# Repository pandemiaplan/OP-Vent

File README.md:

# OP-Vent
A Simple, Open-Source Ventilator using a Proportional Solenoid Valve

Information gathered from https://op-vent.stanford.edu/ check it out!
Article about information at https://www.engadget.com/nvidia-open-source-ventilator-design-165732445.html

- [Code](/code)
- [PCB Design](/OPVentPCB_V2.2)
- [Documentation](https://op-vent.stanford.edu/docs/need.html)
- [Open-Source Pneumatics](https://op-vent.stanford.edu/open-source_pneumatics.html) / [CAD Model](/models/op-vent_open-source-components.STEP)
- [Off-the-Shelf Pneumatics](https://op-vent.stanford.edu/off-the-shelf_pneumatics.html) / [CAD Model](/models/op-vent_off-the-shelf-components.STEP)

## Video Introduction

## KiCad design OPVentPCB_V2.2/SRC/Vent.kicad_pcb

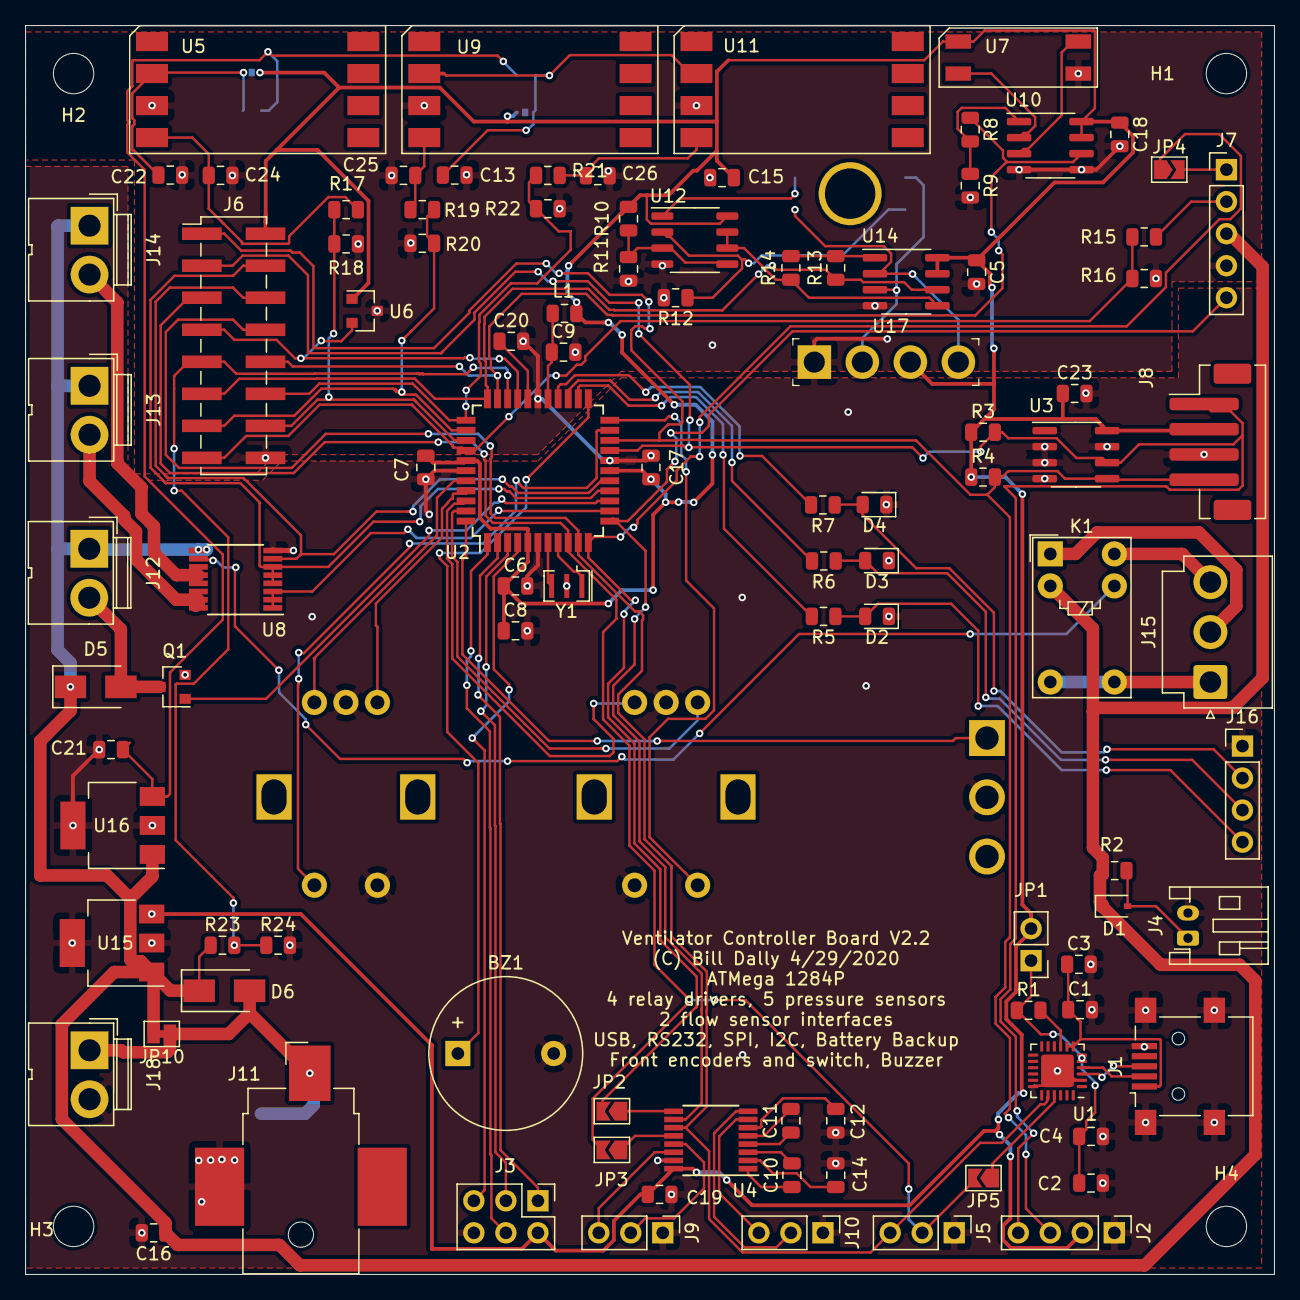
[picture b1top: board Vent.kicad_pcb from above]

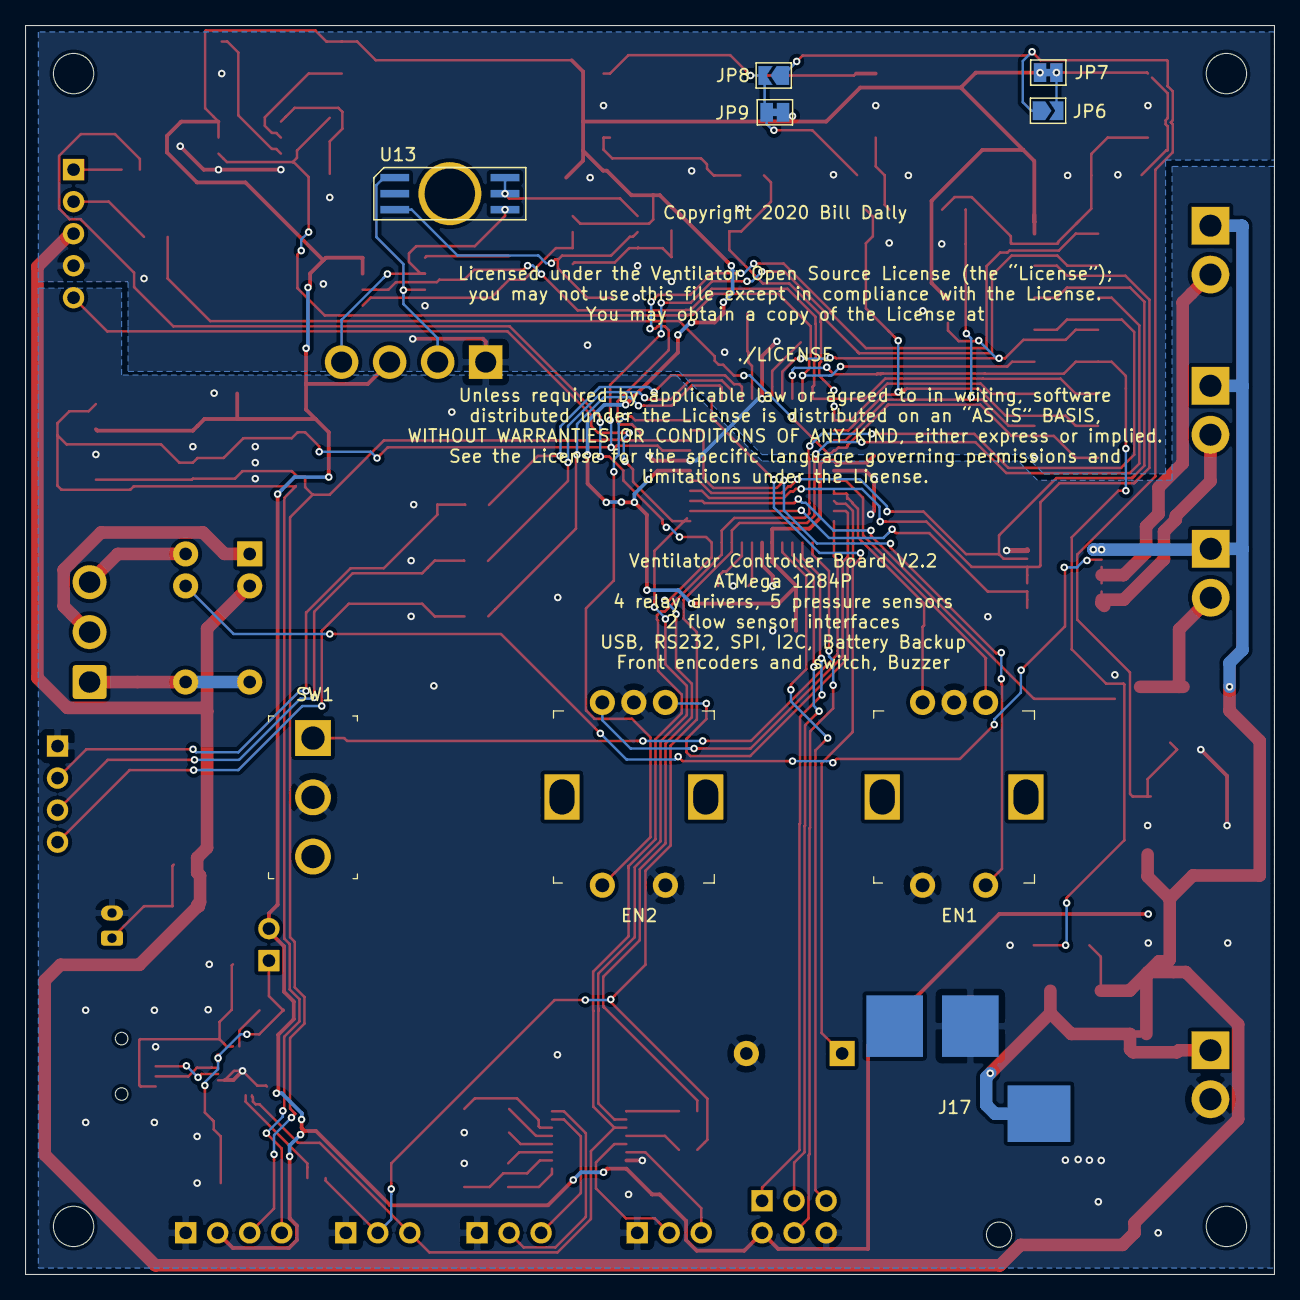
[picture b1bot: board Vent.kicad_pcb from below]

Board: 2 copper layers, 99.1 x 99.1 mm, 113 parts (9 on the bottom side), 88 nets.

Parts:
BZ1: CMI-1295IC-0385T; Buzzer_12x9.5RM7.6
C1, C2: 4.7uF; C_0805_2012Metric
C3, C4, C5, C6, C10, C11, C12, C13, C14, C15, C17, C18, C19, C20, C21, C22, C23: 100nF; C_0805_2012Metric
C7, C16: 10uF; C_0805_2012Metric
C8, C9: 1uF; C_0805_2012Metric
C24, C25, C26: 470pF; C_0805_2012Metric
D1: D_Schottky; D_SOD-323
D2, D3, D4: LED; D_0805_2012Metric
D5, D6: ES1D; D_SMA
EN1: Func_Sel; Rotary_Encoder_Switched_EN11
EN2: Parm_Sel; Rotary_Encoder_Switched_EN11
H1, H2, H3, H4: MountingHole; MountingHole_3.2mm_M3
J1: USB_B_Mini; USB_Mini-B_Lumberg_2486_01_Horizontal
J2: I2C; PinHeader_1x04_P2.54mm_Vertical
J3: Program; PinHeader_2x03_P2.54mm_Vertical
J4: Batt; JST_PH_S2B-PH-K_1x02_P2.00mm_Horizontal
J5: Serial 3.3V; PinHeader_1x03_P2.54mm_Vertical
J6: Test & Spare; PinHeader_2x08_P2.54mm_Vertical_SMD
J7: Siargo; PinHeader_1x05_P2.54mm_Vertical
J8: Honeywell; JST_PH_B4B-PH-SM4-TB_1x04-1MP_P2.00mm_Vertical
J9: RS232; PinHeader_1x03_P2.54mm_Vertical
J10: RS232B; PinHeader_1x03_P2.54mm_Vertical
J11: P12V_Horiz_Front; BarrelJack_CUI_PJ-036AH-SMT_Horizontal
J12: Sol1; JWT_A3963_1x02_P3.96mm_Vertical
J13: Sol2; JWT_A3963_1x02_P3.96mm_Vertical
J14: Sol3; JWT_A3963_1x02_P3.96mm_Vertical
J15: Relay; JST_VH_B3P-VH_1x03_P3.96mm_Vertical
J16: LEDs; PinHeader_1x04_P2.54mm_Vertical
J17: P12V_Vert_Back; BarrelJack_CUI_PJ006A
J18: P12V; JWT_A3963_1x02_P3.96mm_Vertical
JP1: USB Power Jumper; PinHeader_1x02_P2.54mm_Vertical
JP2: RS232B; SolderJumper-2_P1.3mm_Open_TrianglePad1.0x1.5mm
JP3: RS232; SolderJumper-2_P1.3mm_Open_TrianglePad1.0x1.5mm
JP4: Siargo Serial; SolderJumper-2_P1.3mm_Open_TrianglePad1.0x1.5mm
JP5: USB; SolderJumper-2_P1.3mm_Open_TrianglePad1.0x1.5mm
JP6: LP1_5V; SolderJumper-2_P1.3mm_Open_TrianglePad1.0x1.5mm
JP7: LP1_3P3V; SolderJumper-2_P1.3mm_Bridged_Pad1.0x1.5mm
JP8: LP2_5V; SolderJumper-2_P1.3mm_Open_TrianglePad1.0x1.5mm
JP9: LP2_3P3V; SolderJumper-2_P1.3mm_Bridged_Pad1.0x1.5mm
JP10: Power; SolderJumper-2_P1.3mm_Bridged_Pad1.0x1.5mm
K1: G5V-1; Relay_SPDT_Omron_G5V-1
L1: 10uH; L_0805_2012Metric
Q1: PMV20XNE; SOT-23
R1, R3, R4: 2.2K; R_0805_2012Metric
R2, R5, R6, R7: 330; R_0805_2012Metric
R8, R13: 220k; R_0805_2012Metric
R9, R12, R14, R18, R20, R22: 10k; R_0805_2012Metric
R10: 330k; R_0805_2012Metric
R11: 100k; R_0805_2012Metric
R15: 35.7k 0.1%; R_0805_2012Metric
R16: 10k 0.1%; R_0805_2012Metric
R17, R19, R21: 5.1k; R_0805_2012Metric
R23: 26.4K 1%; R_0805_2012Metric
R24: 10k 1%; R_0805_2012Metric
SW1: SW_SPDT; Toggle_Switch_100SP1T1B4M2QE
U1: CP2102N-A01-GQFN24; QFN-24-1EP_4x4mm_P0.5mm_EP2.6x2.6mm
U2: ATmega1284P-AU; TQFP-44_10x10mm_P0.8mm
U3: MC24CM02; SOIC-8_3.9x4.9mm_P1.27mm
U4: MAX3232; TSSOP-16_4.4x5mm_P0.65mm
U5, U11: MP3V5010GP; NXP_Pressure_Sensor
U6: MCP9700AT-ETT; SOT-23
U7: NBPMANN150PGUNV; Honeywell_NBP
U8: ULN2003; TSSOP-16_4.4x5mm_P0.65mm
U9: MPXV5010GP; NXP_Pressure_Sensor
U10, U14: MCP6N11; SOIC-8_3.9x4.9mm_P1.27mm
U12: LMV358; SO-8_3.9x4.9mm_P1.27mm
U13: 2SMPP-03; 2SMPP
U15: 78M33; SOT-223-3_TabPin2
U16: 78L05; SOT-223-3_TabPin2
U17: MX10GP; SIP-4_W3.81mm
Y1: Resonator; Resonator_SMD_muRata_CSTxExxV-3Pin_3.0x1.1mm

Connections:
/A6: J6.9, R23.2, R24.1, U2.31
/A7: J6.7, U2.30, U6.2
/ALARM: BZ1.1, U2.23
/AREF: C20.1, U2.29
/AVCC: C9.1, L1.2, U2.27
/ENC11: EN1.A, U2.40
/ENC12: EN1.B, U2.41
/ENC21: EN2.A, U2.42
/ENC22: EN2.B, U2.43
/FLOW: J6.15, R15.2, R16.1, U2.37
/HP: J6.10, R8.1, U2.32, U10.6
/L1: D2.2, J16.4, R5.1
/L2: D3.2, J16.3, R6.1
/L3: D4.2, J16.2, R7.1
/LED1: R5.2, U2.24
/LED2: R6.2, U2.25
/LED3: R7.2, U2.26
/LP1: J6.14, R17.2, R18.1, U2.36
/LP2: J6.13, R19.2, R20.1, U2.35
/LP3: J6.12, R21.2, R22.1, U2.34
/LP4: J6.11, R13.1, U2.33, U14.6
/MISO: J3.1, U2.2
/MOSI: J3.4, U2.1
/OC1A: Q1.1, U2.14
/OC1B: U2.13, U8.1, U8.2, U8.3
/PD6: J6.4, U2.15, U8.4, U8.5, U8.6
/PD7: J6.6, U2.16, U8.7
/Pressure_Sensors/DLB: R12.1, U12.2, U13.3
/Pressure_Sensors/DLP+: U13.1, U14.3, U17.2
/Pressure_Sensors/DLP-: U13.4, U14.2, U17.4
/Pressure_Sensors/DLPM: R13.2, R14.1, U14.1
/Pressure_Sensors/DLPREF: R14.2, U12.6, U12.7, U14.5
/Pressure_Sensors/DLT: U12.1, U13.5, U13.6
/Pressure_Sensors/HP+: U7.4, U10.3
/Pressure_Sensors/HP-: U7.2, U10.2
/Pressure_Sensors/HPM: R8.2, R9.1, U10.1
/Pressure_Sensors/LP1R: C24.1, R17.1, U5.4
/Pressure_Sensors/LP2R: C25.1, R19.1, U9.4
/Pressure_Sensors/LP3R: C26.1, R21.1, U11.4
/Pressure_Sensors/V1V: R10.2, R11.1, U12.3, U12.5
/Pressure_Sensors/VP1: C22.1, JP6.2, JP7.2, U5.2
/Pressure_Sensors/VP2: C13.1, JP8.2, JP9.2, U9.2, U11.2
/RELAY_C: J15.1, K1.5, K1.6
/RELAY_NC: J15.2, K1.1
/RELAY_NO: J15.3, K1.10
/RESETN: J3.5, U2.4
/RS232/C1+: C10.1, U4.1
/RS232/C1-: C10.2, U4.3
/RS232/C2+: C11.1, U4.4
/RS232/C2-: C11.2, U4.5
/RS232/RR1: J9.2, U4.13
/RS232/RR2: J10.2, U4.8
/RS232/RT1: J9.3, U4.14
/RS232/RT2: J10.3, U4.7
/RS232/VS+: C14.1, U4.2
/RS232/VS-: C12.1, U4.6
/RXD: J5.2, J6.5, JP3.2, JP5.2, U2.9
/RXD1: JP2.2, JP4.1, U2.11
/SCL: J2.4, J6.3, J8.1, R3.2, U2.19, U3.6
/SCLK: J3.3, U2.3
/SDA: J2.3, J6.1, J8.4, R4.2, U2.20, U3.5
/SFLOW: J7.2, R15.1
/SOL1: D5.2, J12.2, Q1.3
/SOL2: J13.2, U8.14, U8.15, U8.16
/SOL3: J14.2, U8.11, U8.12, U8.13
/SOL4: K1.9, U8.10
/SRXD: JP3.1, U4.12
/SRXD1: JP2.1, U4.9
/STX: J7.1, JP4.2
/SW1: SW1.1, U2.44
/SW2: EN1.S1, U2.21
/SW3: EN2.S2, U2.22
/TXD: J5.3, J6.8, U1.20, U2.10, U4.11
/TXD1: J7.5, U2.12, U4.10
/URXD: JP5.1, U1.21
/USB_Serial/D+: J1.3, U1.3
/USB_Serial/D-: J1.2, U1.4
/USB_Serial/URST_N: R1.2, U1.9
/USB_Serial/USB_VCC: C2.1, C4.1, JP1.1, R1.1, U1.5, U1.6
/USB_Serial/VBUS: C1.1, C3.1, J1.1, U1.7, U1.8
/V5: C21.1, JP6.1, JP8.1, U16.3
/V12: C16.1, D1.1, D5.1, D6.1, J7.3, J12.1, J13.1, J14.1, JP10.2, K1.2, R2.2, R23.1, U8.9, U15.1, U16.1
/V12A: D6.2, J11.1, J17.1, J18.1, JP10.1
/XTAL1: U2.8, Y1.1
/XTAL2: U2.7, Y1.3
GND: BZ1.2, C1.2, C2.2, C3.2, C4.2, C5.2, C6.2, C7.2, C8.2, C9.2, C12.2, C13.2, C14.2, C15.2, C16.2, C17.2, C18.2, C19.2, C20.2, C21.2, C22.2, C23.2, C24.2, C25.2, C26.2, D2.1, D3.1, D4.1, EN1.C, EN1.S2, EN2.C, EN2.S1, J1.5, J1.6, J2.1, J3.6, J4.2, J5.1, J6.16, J7.4, J8.3, J9.1, J10.1, J11.2, J16.1, J17.2, J18.2, Q1.2, R9.2, R11.2, R12.2, R16.2, R18.2, R20.2, R22.2, R24.2, SW1.2, U1.2, U1.18, U1.25, U2.6, U2.18, U2.28, U2.39, U3.2, U3.3, U3.4, U3.7, U4.15, U5.3, U6.3, U7.3, U8.8, U9.3, U10.4, U10.5, U11.3, U12.4, U14.4, U15.2, U16.2, U17.1, Y1.2
unnamed: D1.2, J4.1, R2.1
VCC: C5.1, C6.1, C7.1, C8.1, C15.1, C17.1, C18.1, C19.1, C23.1, J2.2, J3.2, J6.2, J8.2, JP1.2, JP7.1, JP9.1, L1.1, R3.1, R4.1, R10.1, U2.5, U2.17, U2.38, U3.8, U4.16, U6.1, U7.1, U10.7, U10.8, U12.8, U14.7, U14.8, U15.3, U17.3

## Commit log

2020-05-04 Update LICENSE
    update based on https://op-vent.stanford.edu/license.pdf
2020-05-04 updated models from OP-Vent

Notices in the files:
OPVentPCB_V2.2/SRC/Vent.kicad_pcb:
Copyright 2020 Bill Dally
Licensed under the Ventilator Open Source License (the “License”);
